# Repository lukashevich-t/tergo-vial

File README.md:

### Фичи:

- Раскладка Jiran (ну, почти...)
- Backlight
- Двойной shift работает как Enter
- Отображение состояния Caps/Num lock на экране
- отображение на экране текущего слоя клавы
- Отображение на экране активного на компе языка ввода (нужен агент на компе)
- Отображение активного на компе языка ввода в виде горящей/погасшей подсветки (нужен агент на компе)
- Активация режима Bootloader:
  - Если сбросить при нажатой кнопке 3 (только для левой половины)
  - Если на 3-м слое нажать 3 (на левой половине) или 8 (на правой)
  - Если сбросить при нажатой кнопке Boot на макетке (стандарт для RP2040)
  - "двойной клик" по сбросу
- На 3-м управляющем слое кнопка 5 (6) выдаёт на экран логотип и выплёвывает кой-какую информацию в debug console

### Структура папок

```
.
├── hardware                     # железная часть проекта
│   ├── case                     # Проекты корпусов
│   │   ├── tergo-choc           # Корпус для варианта tergo-choc
│   │   └── tergo-mx             # Корпус для варианта tergo-mx
│   ├── pcb                      # Проекты печатных плат
│   │   ├── 3rd-party-libs       # Сторонние библиотеки, откуда я взял символы и посадочные места для проектирования PCB
│   │   ├── common               #
│   │   │   └── libs             # Моя сборная библиотека символов и посадочных мест для KiCAD. Этот путь нужно прописать в Kicad в переменную TERGO_LIBS ("Preferences -> Configure paths")
│   │   ├── tergo-choc           # PCB для варианта tergo-choc
│   │   └── tergo-mx             # PCB для варианта tergo-mx
│   └── temp                     # Всякие временные тестовые файлы для прототипирования (KiCAD, FreeCAD...). Не для хранения в git
├── host-software                # ПО для ПК (взаимодействие ПК с клавиатурой)
│   ├── cinnamon-extension       # расширение для Cinnamon desktop для отображения текущей раскладки клавиатуры на экране клавиатуры
│   ├── cinnamon-extension-old   # предыдущая реализация (на javascript) расширения для Cinnamon desktop для отображения текущей раскладки клавиатуры на экране клавиатуры
│   └── windows-QmkLayoutMonitor # агент для Windows для отображения текущей раскладки клавиатуры на экране клавиатуры
├── layouts                      # Исходные коды прошивки для различных вариантов
│   ├── tergo-choc               # прошивка QMK-vial для варианта на low-profile свичах Kailh choc v1 (1350)
│   │   └── common.h             # Тут описаны отладочные макроопределения, которые могут печатать значения других макроопределений во время компиляции. Как использовать, см. ниже
│   └── tergo-mx                 # прошивка QMK-vial для варианта на свичах Cherry MX
│       └── common.h             # см. выше
└── logo                         # Битмап логотипа и шрифт, которым он напечатан. Скрипт для создания проявляющегося лого (см. инструкцию ниже)
    └── old_scripts              # старые скрипты для перегона битмапов в массив байтов для экрана. после отказа от драйвера OLED (перешел на Quantum painter) - потеряли актуальность.
/mnt/media/work/vial-qmk/keyboards/tergo/layouts/layout-tergo-mx/common.h
```

Пример использования отладочных макроопределений из файла `common.h`:

```c
#pragma message "RAW_USAGE_ID " DESCRIBE_MACRO_VALUE(RAW_USAGE_ID)
#pragma message DESCRIBE_MACRO(QMK_KEYBOARD_H)
```

### Preparation

- TBD...
- After cloning git repository, go to Kicad path variables and define variable `TERGO_LIBS` to point to <repo>/pcb/common/libs, i.e.: `TERGO_LIBS => /home/tim/work/qmk_firmware/keyboards/tergo/pcb/common/libs`

### Печать корпуса

- Примечание: иногда при экспорте файлов STL из проекта freecad они получаются битые - слайсер ругается на них. В этом случае попробовать отключить/включить активность импортируемого тела, поворочать, экспортировать снова... Короче, поплясать с бубном.
- Из проекта Freecad (`./case/case-left.FCStd`) экспортировать в формат STL тело "full-top-new" - это верх левой половины.
- Верх правой половины получить средствами слайсера (отзеркалить).
- Напечатать.
- Эспортировать тела "full-bottom-new-left-with-logo" и "full-bottom-new-left-with-logo".
- Напечатать.

### Отображение раскладки клавиатуры

- скомпилить поддержку HID RAW (`RAW_ENABLE = yes` и обработчик сообщений).
- прошить в клаву
- для Linux Mint cinnamon edition использовать проект `_cinnamon-extension` или `_cinnamon-extension-old`
- Для Windows собрать `_windows-QmkLayoutMonitor` в соответствии с инструкцией в папке

### Логотип

- Подготовить файл `logo/logo.png` с разрешением 320x1280 пикселей (вертикальная ориентация). Лучше всего будет смотреться белые буквы на черном фоне.
- В скрипте `logo/create-logo-animation.py` подобрать под себя количество и длительность кадров анимации.
- Если логотип скорее черный на белом, придётся подправить скрипт:
  - `if img_1bit.getpixel((x, y)) > 0:` заменить на `if img_1bit.getpixel((x, y)) == 0:`
  - `current_frame.putpixel(px, 255)` заменить на `current_frame.putpixel(px, 0)`
- запустить питонский скрипт:

```bash
cd logo
python3 create-logo-animation.py
```

- появится папка с отдельными кадрами, а также анимированный файл `logo.gif`
- натравить на него преобразователь картинок:

```bash
rm -rf converted-image && mkdir -p converted-image && qmk painter-convert-graphics -f mono2 -o ./converted-image -i logo.gif
```

- содержимое папки `logo/converted-image/logo.qgf.*` переписать в `split/display/` с заменой файлов.
- Пересобрать прошивку.

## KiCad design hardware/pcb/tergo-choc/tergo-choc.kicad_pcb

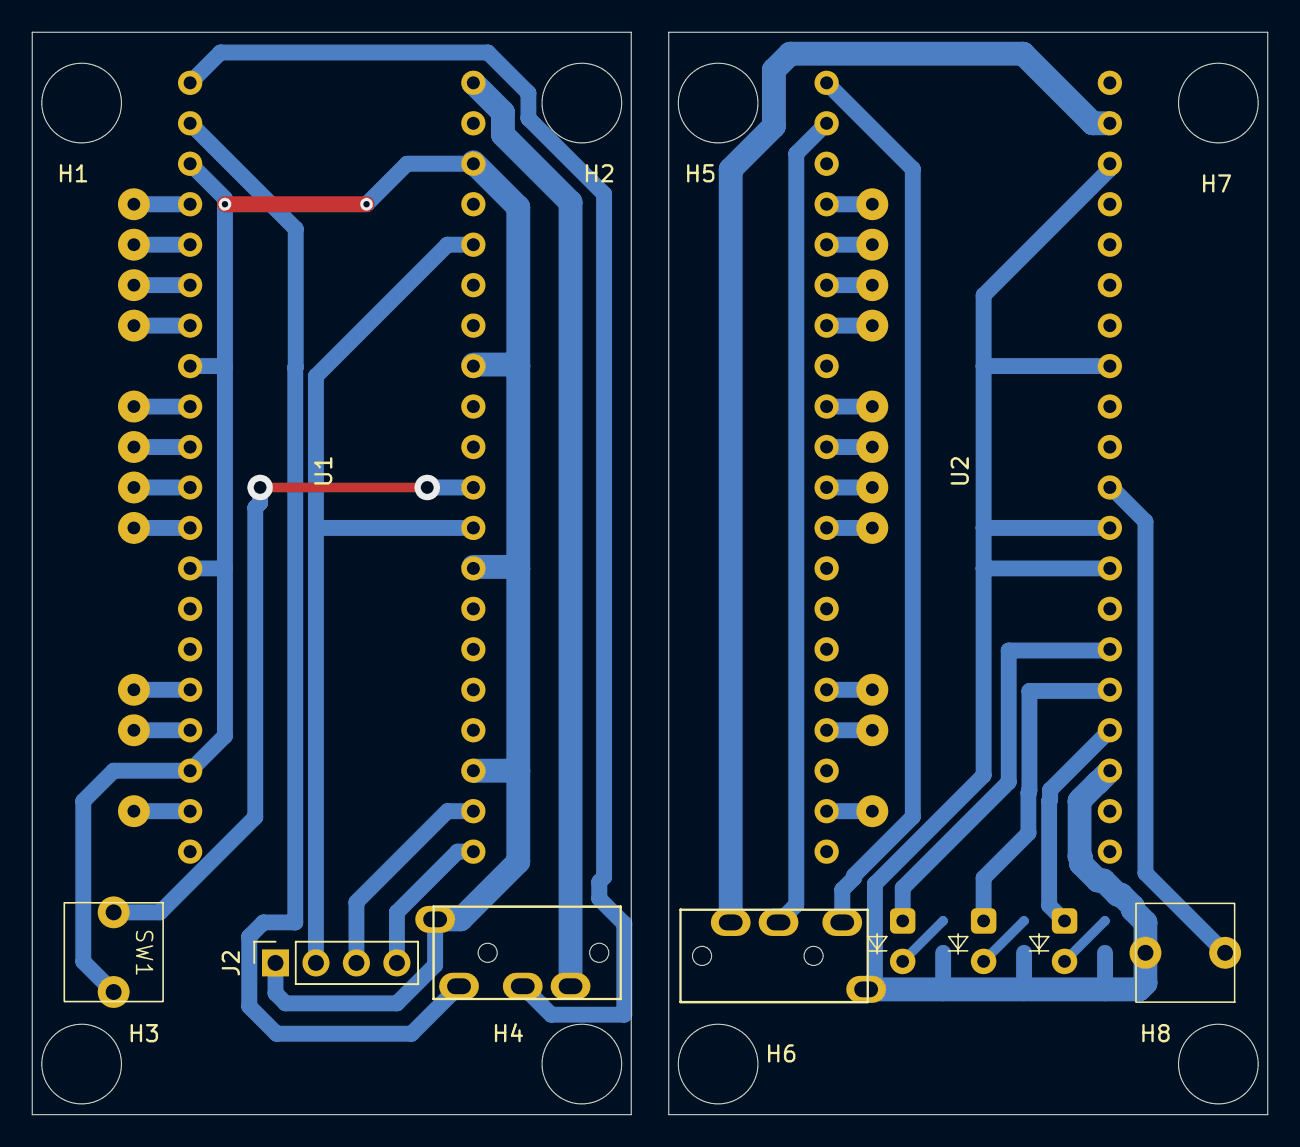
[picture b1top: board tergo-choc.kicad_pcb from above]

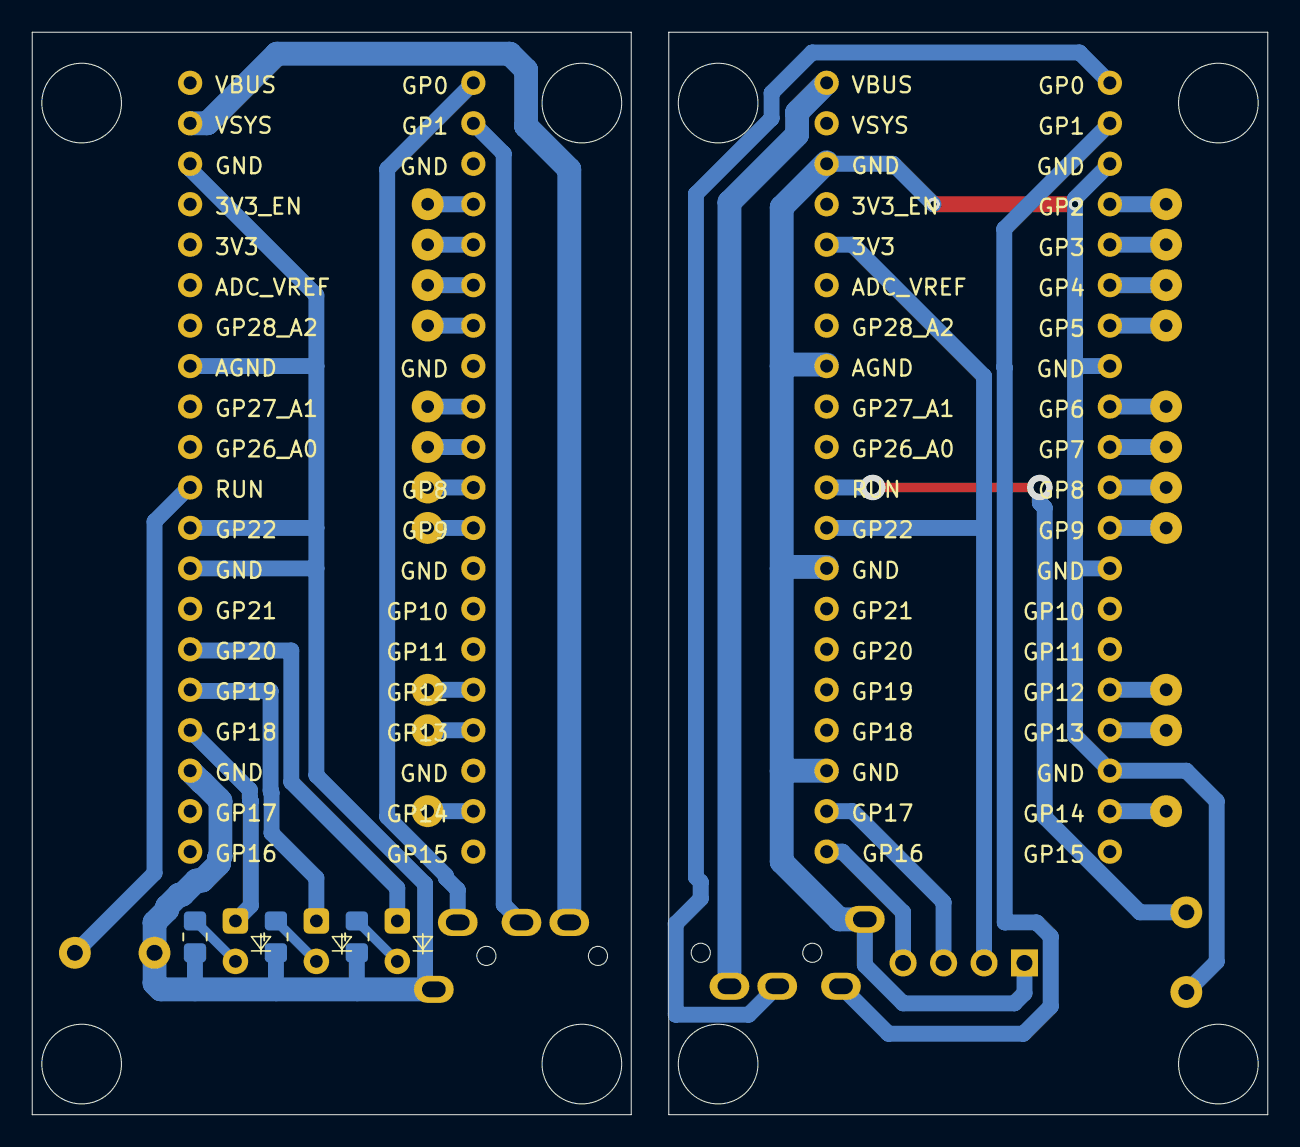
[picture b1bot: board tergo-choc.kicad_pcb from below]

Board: 2 copper layers, 77.6 x 67.9 mm, 43 parts (3 on the bottom side), 40 nets.

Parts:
D10: NL; LED_1.8mm
D59: CL; LED_1.8mm
D60: SL; LED_1.8mm
H1, H2, H3, H4, H5, H6, H7, H8: MountingHole; MountHole_5mm
J1, J3: TRRS_SOCKET; MJ-4PP-9
J2: Conn_01x04_Socket; PinSocket_1x04_P2.54mm_Vertical
J12, J13, J14, J15, J18, J19, J20, J21, J22, J23, J24, J25, J26, J27, J28, J29, J30, J31, J32, J33, J34, J35: Conn_01x01_Socket; THT_PAD
R1, R3, R4: R_Small; R_0805_2012Metric_Pad1.20x1.40mm_HandSolder
SW1: RST_LEFT; pushbutton-THT-2pin
SW30: RST_RIGHT; pushbutton-THT-2pin
U1, U2: Raspberry_Pi_Pico

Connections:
/3V3_L: J2.2, U1.29 (GP22), U1.36 (3V3)
/CAPS_LOCK: D59.2 (A), U2.25 (GP19)
/COL0_L: J12.1 (Pin_1_1), U1.4 (GP2)
/COL0_R: J25.1 (Pin_1_1), U2.4 (GP2)
/COL1_L: J15.1 (Pin_1_1), U1.7 (GP5)
/COL1_R: J28.1 (Pin_1_1), U2.7 (GP5)
/COL2_L: J14.1 (Pin_1_1), U1.6 (GP4)
/COL2_R: J27.1 (Pin_1_1), U2.6 (GP4)
/COL3_L: J19.1 (Pin_1_1), U1.10 (GP7)
/COL3_R: J30.1 (Pin_1_1), U2.10 (GP7)
/COL4_L: J20.1 (Pin_1_1), U1.11 (GP8)
/COL4_R: J31.1 (Pin_1_1), U2.11 (GP8)
/COL5_L: J21.1 (Pin_1_1), U1.12 (GP9)
/COL5_R: J32.1 (Pin_1_1), U2.12 (GP9)
/DISPLAY_SCL: J2.3, U1.22 (GP17/SCL)
/DISPLAY_SDA: J2.4, U1.21 (GP16/SDA)
/NUM_LOCK: D10.2 (A), U2.26 (GP20)
/ROWA_L: J13.1 (Pin_1_1), U1.5 (GP3)
/ROWA_R: J26.1 (Pin_1_1), U2.5 (GP3)
/ROWB_L: J18.1 (Pin_1_1), U1.9 (GP6)
/ROWB_R: J29.1 (Pin_1_1), U2.9 (GP6)
/ROWC_L: J22.1 (Pin_1_1), U1.16 (GP12)
/ROWC_R: J33.1 (Pin_1_1), U2.16 (GP12)
/ROWD_L: J23.1 (Pin_1_1), U1.17 (GP13)
/ROWD_R: J34.1 (Pin_1_1), U2.17 (GP13)
/ROWE_L: J24.1 (Pin_1_1), U1.19 (GP14)
/ROWE_R: J35.1 (Pin_1_1), U2.19 (GP14)
/RST_L: SW1.1 (C), U1.30 (RUN)
/RST_R: SW30.1 (C), U2.30 (RUN)
/RX_L: J1.D, U1.2 (GP1/RX)
/RX_R: J3.C, U2.2 (GP1/RX)
/SCROLL_LOCK: D60.2 (A), U2.24 (GP18)
/TX_L: J1.C, U1.1 (GP0/TX)
/TX_R: J3.D, U2.1 (GP0/TX)
/VIN_R: J3.B, U2.39 (Vin)
/VOUT_L: J1.B, U1.40 (Vout)
GND: J1.A, J2.1, J3.A, R1.2, R3.2, R4.2, SW1.2 (D), SW30.2 (D), U1.3 (GND), U1.8 (GND), U1.13 (GND), U1.18 (GND), U1.23 (GND), U1.28 (GND), U1.33 (AGND), U1.38 (GND), U2.23 (GND), U2.28 (GND), U2.29 (GP22), U2.33 (AGND), U2.38 (GND)
unnamed: D10.1 (K), R1.1
unnamed: D59.1 (K), R3.1
unnamed: D60.1 (K), R4.1

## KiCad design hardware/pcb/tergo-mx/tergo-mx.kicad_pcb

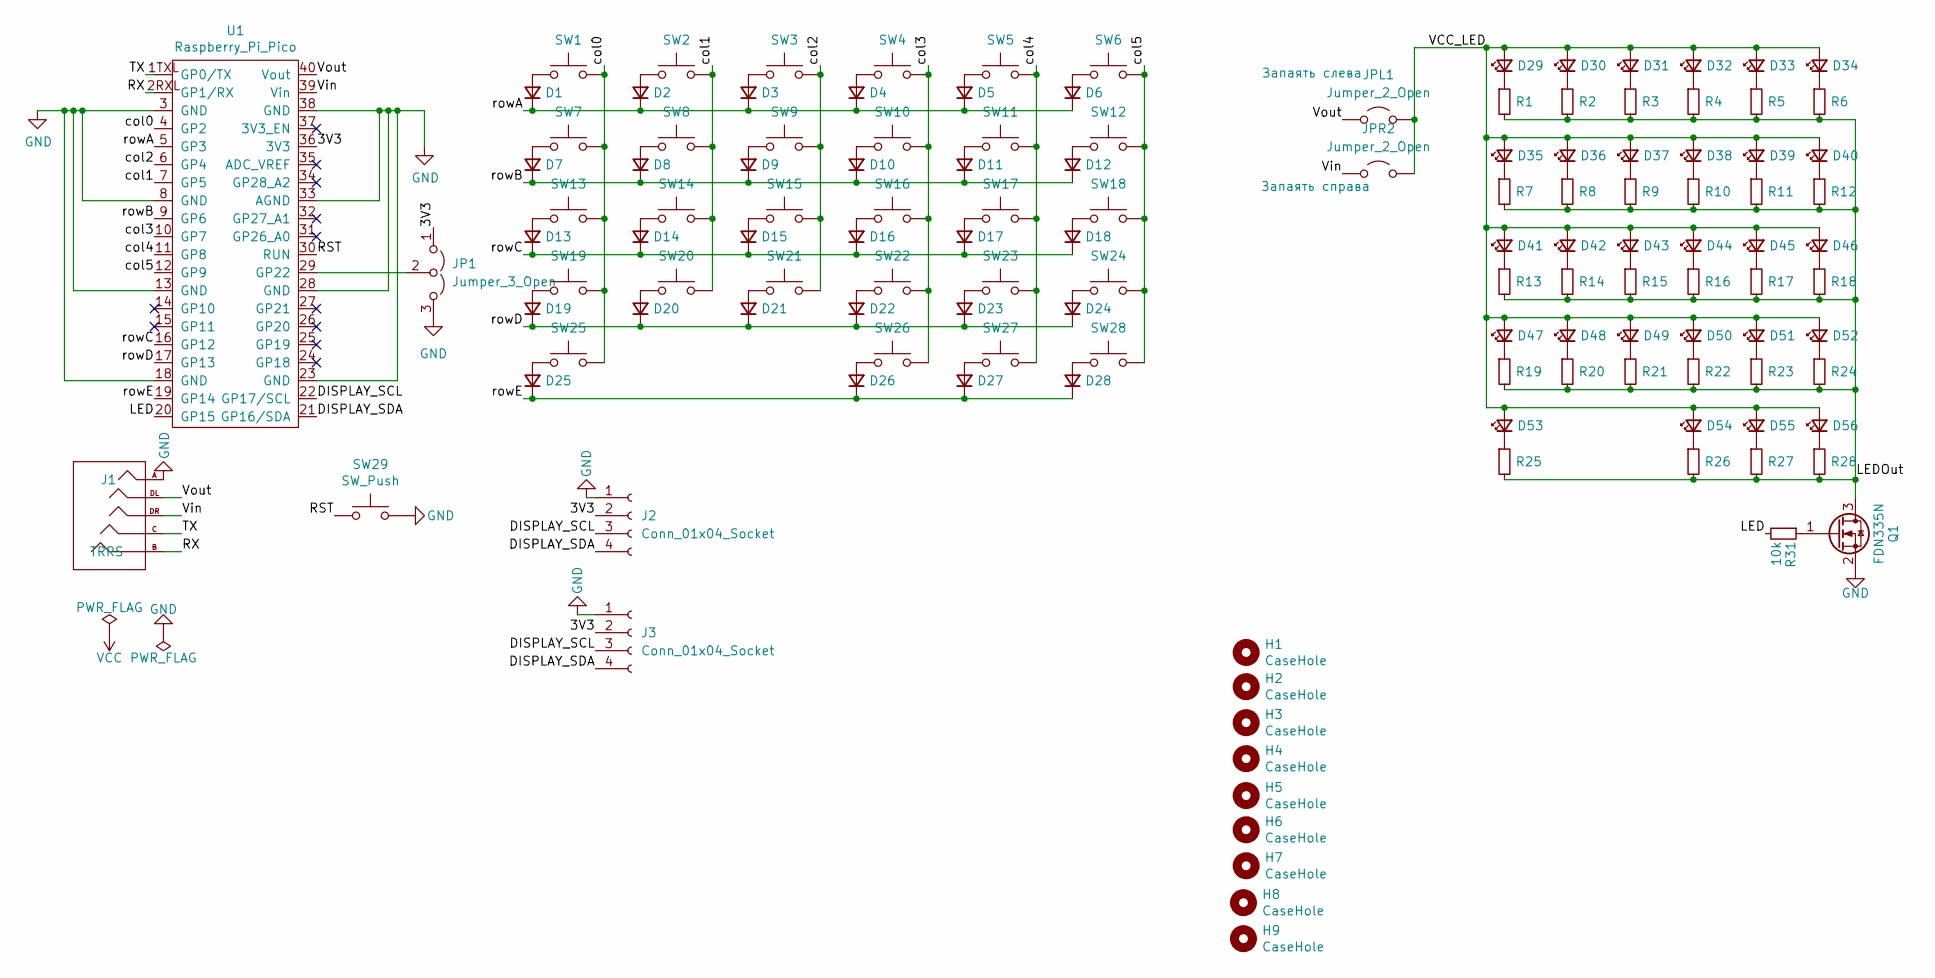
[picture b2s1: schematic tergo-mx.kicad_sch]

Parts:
D1, D2, D3, D4, D5, D6, D7, D8, D9, D10, D11, D12, D13, D14, D15, D16, D17, D18, D19, D20, D21, D22, D23, D24, D25, D26, D27, D28: D_Small; Diode-Hybrid-2sided
D29, D30, D31, D32, D33, D34, D35, D36, D37, D38, D39, D40, D41, D42, D43, D44, D45, D46, D47, D48, D49, D50, D51, D52, D53, D54, D55, D56: LED_Small; LED_1.8mm
H1, H2, H3, H4, H5, H6, H7, H8, H9: CaseHole; MountHole
J1: TRRS; MJ-4PP-9-mirrored
J2, J3: Conn_01x04_Socket; PinHeader_1x04_P2.54mm_Vertical
JP1: Jumper_3_Open; SolderJumper-3_P1.3mm_Open_RoundedPad1.0x1.5mm
JPL1: Jumper_2_Open; SolderJumper-2_P1.3mm_Open_RoundedPad1.0x1.5mm
JPR2: Jumper_2_Open; SolderJumper-2_P1.3mm_Open_RoundedPad1.0x1.5mm
Q1: FDN335N; SOT-23
R1, R2, R3, R4, R5, R6, R7, R8, R9, R10, R11, R12, R13, R14, R15, R16, R17, R18, R19, R20, R21, R22, R23, R24, R25, R26, R27, R28: R_Small; Resistor-Hybrid-2sided
R31: 10k; Resistor-Hybrid-2sided
SW1, SW2, SW3, SW4, SW5, SW6, SW7, SW8, SW9, SW10, SW11, SW12, SW13, SW14, SW15, SW16, SW17, SW18, SW19, SW20, SW21, SW22, SW23, SW24, SW25, SW26, SW27, SW28: SW_Push; SW_Hotswap_Kailh_MX_Plated_mirrored2_1.00u
SW29: SW_Push; ResetSW
U1: Raspberry_Pi_Pico; Raspberry_Pi_Pico_dual

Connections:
/3V3: J2.2, J3.2, JP1.1 (A), U1.36 (3V3)
/DISPLAY_SCL: J2.3, J3.3, U1.22 (GP17/SCL)
/DISPLAY_SDA: J2.4, J3.4, U1.21 (GP16/SDA)
/LED: R31.2, U1.20 (GP15)
/LEDOut: Q1.3 (D), R1.2, R2.2, R3.2, R4.2, R5.2, R6.2, R7.2, R8.2, R9.2, R10.2, R11.2, R12.2, R13.2, R14.2, R15.2, R16.2, R17.2, R18.2, R19.2, R20.2, R21.2, R22.2, R23.2, R24.2, R25.2, R26.2, R27.2, R28.2
/RST: SW29.1, U1.30 (RUN)
/RX: J1.B, U1.2RXL (GP1/RX)
/TX: J1.C, U1.1TXL (GP0/TX)
/VCC_LED: D29.2 (A), D30.2 (A), D31.2 (A), D32.2 (A), D33.2 (A), D34.2 (A), D35.2 (A), D36.2 (A), D37.2 (A), D38.2 (A), D39.2 (A), D40.2 (A), D41.2 (A), D42.2 (A), D43.2 (A), D44.2 (A), D45.2 (A), D46.2 (A), D47.2 (A), D48.2 (A), D49.2 (A), D50.2 (A), D51.2 (A), D52.2 (A), D53.2 (A), D54.2 (A), D55.2 (A), D56.2 (A), JPL1.2 (B), JPR2.2 (B)
/Vin: J1.DR, JPR2.1 (A), U1.39 (Vin)
/Vout: J1.DL, JPL1.1 (A), U1.40 (Vout)
/col0: SW1.2, SW7.2, SW13.2, SW19.2, SW25.2, U1.4 (GP2)
/col1: SW2.2, SW8.2, SW14.2, SW20.2, U1.7 (GP5)
/col2: SW3.2, SW9.2, SW15.2, SW21.2, U1.6 (GP4)
/col3: SW4.2, SW10.2, SW16.2, SW22.2, SW26.2, U1.10 (GP7)
/col4: SW5.2, SW11.2, SW17.2, SW23.2, SW27.2, U1.11 (GP8)
/col5: SW6.2, SW12.2, SW18.2, SW24.2, SW28.2, U1.12 (GP9)
/rowA: D1.1 (K), D2.1 (K), D3.1 (K), D4.1 (K), D5.1 (K), D6.1 (K), U1.5 (GP3)
/rowB: D7.1 (K), D8.1 (K), D9.1 (K), D10.1 (K), D11.1 (K), D12.1 (K), U1.9 (GP6)
/rowC: D13.1 (K), D14.1 (K), D15.1 (K), D16.1 (K), D17.1 (K), D18.1 (K), U1.16 (GP12)
/rowD: D19.1 (K), D20.1 (K), D21.1 (K), D22.1 (K), D23.1 (K), D24.1 (K), U1.17 (GP13)
/rowE: D25.1 (K), D26.1 (K), D27.1 (K), D28.1 (K), U1.19 (GP14)
GND: J1.A, J2.1, J3.1, JP1.3 (B), Q1.2 (S), SW29.2, U1.3 (GND), U1.8 (GND), U1.13 (GND), U1.18 (GND), U1.23 (GND), U1.28 (GND), U1.33 (AGND), U1.38 (GND)
unnamed: D1.2 (A), SW1.1
unnamed: D2.2 (A), SW2.1
unnamed: D3.2 (A), SW3.1
unnamed: D4.2 (A), SW4.1
unnamed: D5.2 (A), SW5.1
unnamed: D6.2 (A), SW6.1
unnamed: D7.2 (A), SW7.1
unnamed: D8.2 (A), SW8.1
unnamed: D9.2 (A), SW9.1
unnamed: D10.2 (A), SW10.1
unnamed: D11.2 (A), SW11.1
unnamed: D12.2 (A), SW12.1
unnamed: D13.2 (A), SW13.1
unnamed: D14.2 (A), SW14.1
unnamed: D15.2 (A), SW15.1
unnamed: D16.2 (A), SW16.1
unnamed: D17.2 (A), SW17.1
unnamed: D18.2 (A), SW18.1
unnamed: D19.2 (A), SW19.1
unnamed: D20.2 (A), SW20.1
unnamed: D21.2 (A), SW21.1
unnamed: D22.2 (A), SW22.1
unnamed: D23.2 (A), SW23.1
unnamed: D24.2 (A), SW24.1
unnamed: D25.2 (A), SW25.1
unnamed: D26.2 (A), SW26.1
unnamed: D27.2 (A), SW27.1
unnamed: D28.2 (A), SW28.1
unnamed: D29.1 (K), R1.1
unnamed: D30.1 (K), R2.1
unnamed: D31.1 (K), R3.1
unnamed: D32.1 (K), R4.1
unnamed: D33.1 (K), R5.1
unnamed: D34.1 (K), R6.1
unnamed: D35.1 (K), R7.1
unnamed: D36.1 (K), R8.1
unnamed: D37.1 (K), R9.1
unnamed: D38.1 (K), R10.1
unnamed: D39.1 (K), R11.1
unnamed: D40.1 (K), R12.1
unnamed: D41.1 (K), R13.1
unnamed: D42.1 (K), R14.1
unnamed: D43.1 (K), R15.1
unnamed: D44.1 (K), R16.1
unnamed: D45.1 (K), R17.1
unnamed: D46.1 (K), R18.1
unnamed: D47.1 (K), R19.1
unnamed: D48.1 (K), R20.1
unnamed: D49.1 (K), R21.1
unnamed: D50.1 (K), R22.1
unnamed: D51.1 (K), R23.1
unnamed: D52.1 (K), R24.1
unnamed: D53.1 (K), R25.1
unnamed: D54.1 (K), R26.1
unnamed: D55.1 (K), R27.1
unnamed: D56.1 (K), R28.1
unnamed: JP1.2 (C), U1.29 (GP22)
unnamed: Q1.1 (G), R31.1

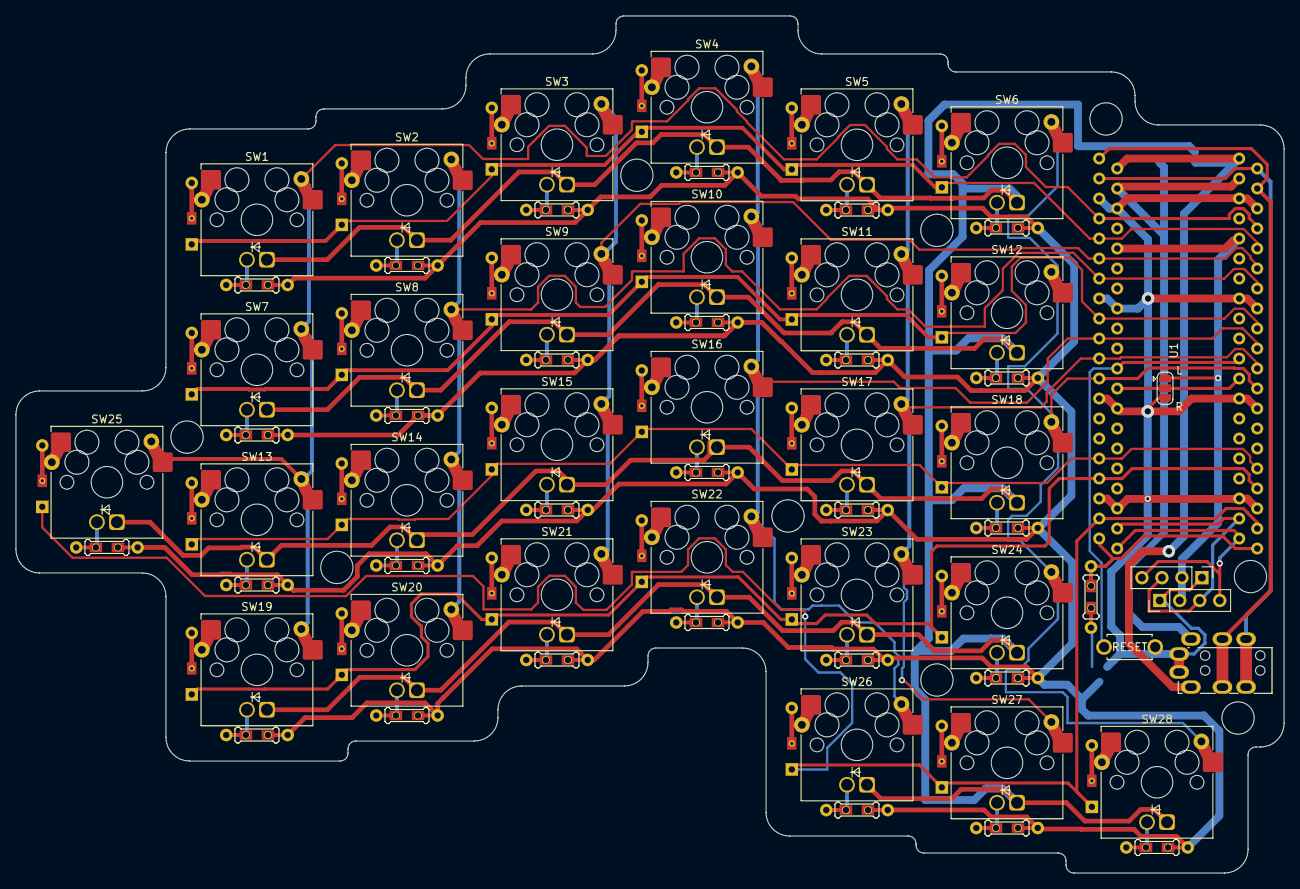
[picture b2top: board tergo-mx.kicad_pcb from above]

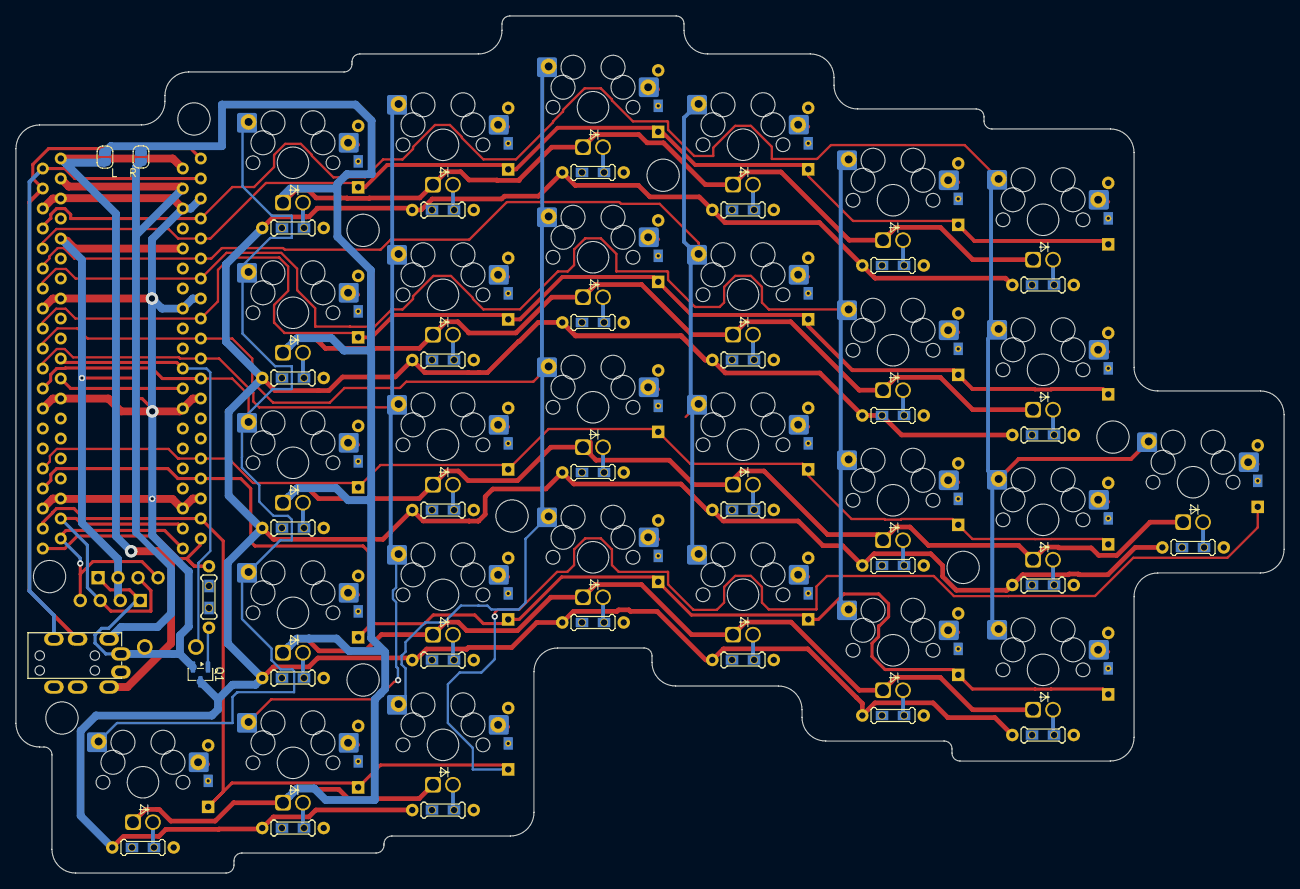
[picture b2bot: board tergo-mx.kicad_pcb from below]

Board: 2 copper layers, 161.0 x 108.8 mm, 131 parts (3 on the bottom side), 81 nets.

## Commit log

2026-04-09 fixed config.h. added case projects for Cherry MX and Kailh chok variants
2026-04-10 reorganized folders
2026-04-19 reorganize folders structure
2026-04-28 added keycap engrave macro for FreeCAD
2026-04-28 keycap engrave refactoring
2026-04-29 FreeCAD macro for engrave keycaps IS READY!
2026-05-04 choc pcb - layout
2026-05-10 semi-completed case for tergo-choc renamed directories
2026-05-10 renamed directories
2026-05-26 couple of fixes in tergo-choc case
2026-05-29 keycap script
2026-05-30 - Реализация расширения для Gnome desktop для передачи названия текущей раскладки в клавиатуру - Поменял местами PgUp/PgDn и Home/End - Задействовал светодиод Scroll Lock как индикатор не-английской 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
